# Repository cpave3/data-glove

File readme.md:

# Data-Glove

All of the assets related to my data glove prototype

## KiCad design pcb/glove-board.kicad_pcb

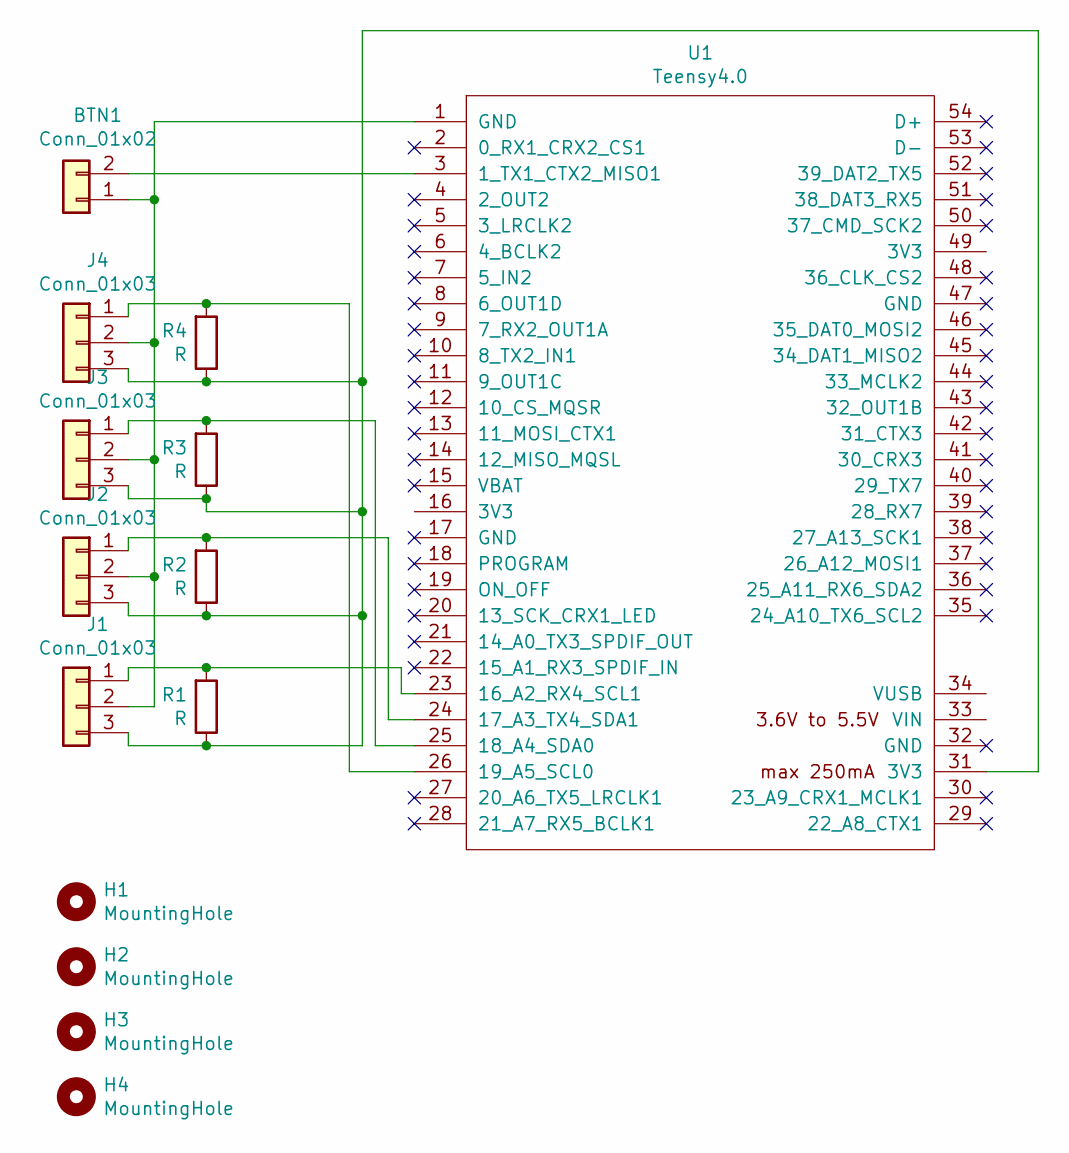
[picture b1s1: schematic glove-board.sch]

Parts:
BTN1: Conn_01x02; JST_XH_B2B-XH-A_1x02_P2.50mm_Vertical
H1, H2, H3, H4: MountingHole; MountingHole_2.2mm_M2_ISO7380
J1, J2, J3, J4: Conn_01x03; JST_XH_B3B-XH-A_1x03_P2.50mm_Vertical
R1, R2, R3, R4: R; R_Axial_DIN0207_L6.3mm_D2.5mm_P10.16mm_Horizontal
U1: Teensy4.0; Teensy40

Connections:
unnamed: BTN1.1, J1.2, J2.2, J3.2, J4.2, U1.1 (GND)
unnamed: BTN1.2, U1.3 (1_TX1_CTX2_MISO1)
unnamed: J1.1, R1.2, U1.23 (16_A2_RX4_SCL1)
unnamed: J1.3, J2.3, J3.3, J4.3, R1.1, R2.1, R3.1, R4.1, U1.31 (3V3)
unnamed: J2.1, R2.2, U1.24 (17_A3_TX4_SDA1)
unnamed: J3.1, R3.2, U1.25 (18_A4_SDA0)
unnamed: J4.1, R4.2, U1.26 (19_A5_SCL0)

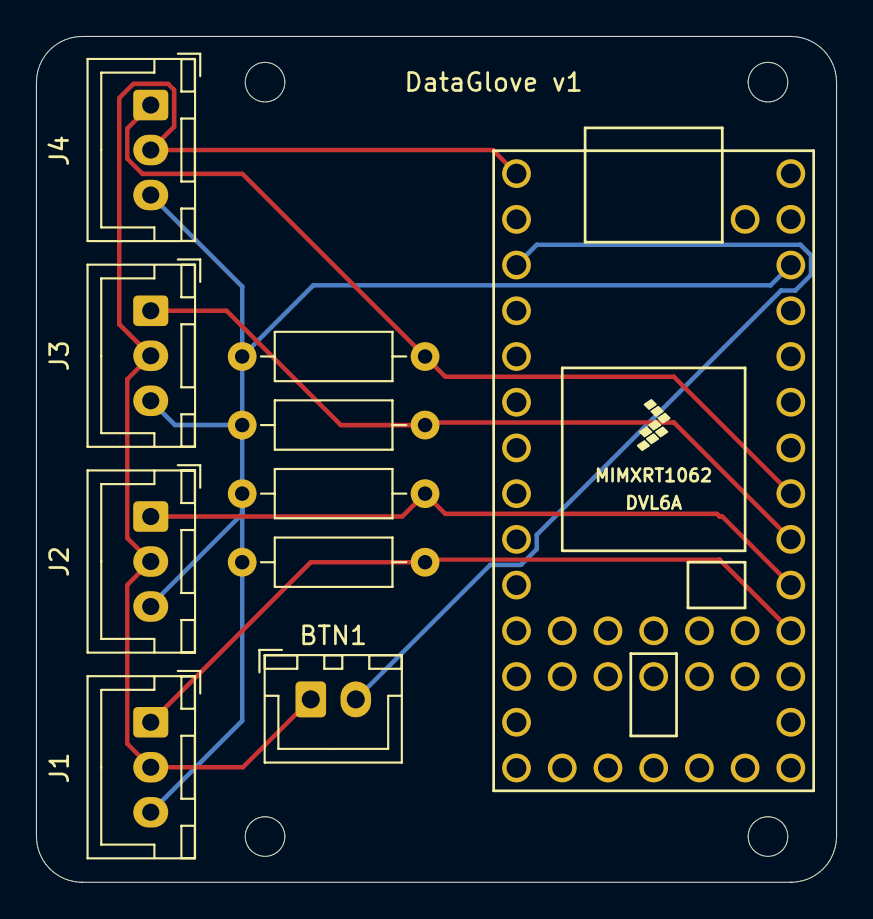
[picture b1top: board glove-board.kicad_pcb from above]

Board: 2 copper layers, 44.4 x 47.0 mm, 14 parts (0 on the bottom side), 7 nets.

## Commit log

2021-10-20 Add updated firmware from prototype
2021-11-27 Initializing Swimm
2021-11-27 docs(swimm): create document Test doc
